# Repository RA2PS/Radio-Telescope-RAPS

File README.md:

# Radio-Telescope-RCA
Radio Telescope System for 1 GHz to 2 GHz Operation

> [!important]
> Make sure to add a KiCad path variable named "RADIO_TELESCOPE_RAPS_PATH"
> for the symbols and footprint to be found on your machine.

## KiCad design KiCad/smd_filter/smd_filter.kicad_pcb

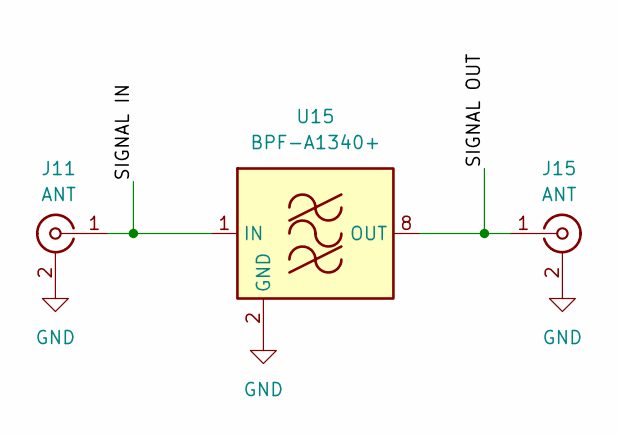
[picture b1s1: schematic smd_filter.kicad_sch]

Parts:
J11, J15: ANT; CONN_142-0711-821_CIN
U15: BPF-A1340+; Mini-Circuits_HQ1157

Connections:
/SMDFilter/GND: J11.2 (Ext), J15.2 (Ext), U15.2 (GND), U15.3 (GND), U15.4 (GND), U15.5 (GND), U15.6 (GND), U15.7 (GND), U15.9 (GND), U15.10 (GND), U15.11 (GND), U15.12 (GND), U15.13 (GND), U15.14 (GND)
/SMDFilter/SIGNAL_IN: J11.1 (In), U15.1 (IN)
/SMDFilter/SIGNAL_OUT: J15.1 (In), U15.8 (OUT)

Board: 2 copper layers, 3 parts (0 on the bottom side), 3 nets, no tracks yet.

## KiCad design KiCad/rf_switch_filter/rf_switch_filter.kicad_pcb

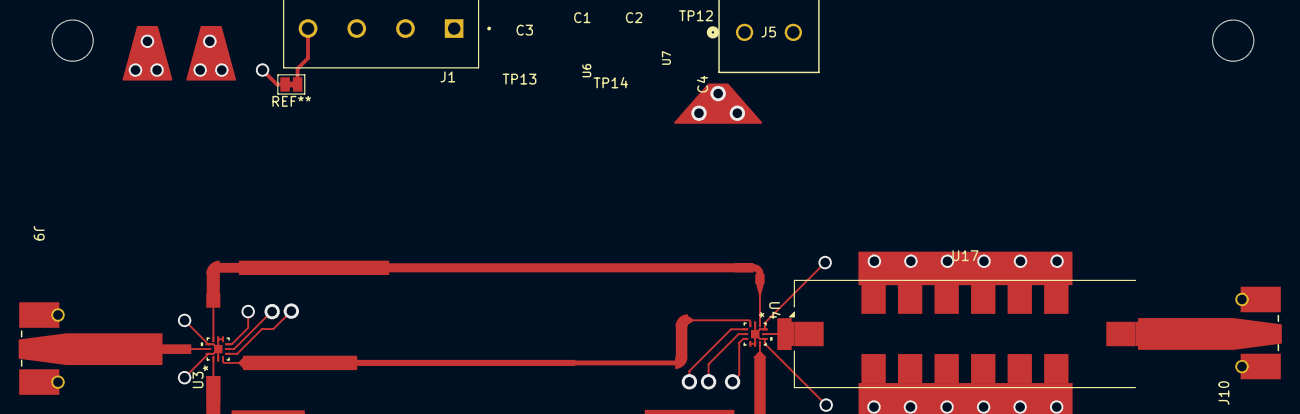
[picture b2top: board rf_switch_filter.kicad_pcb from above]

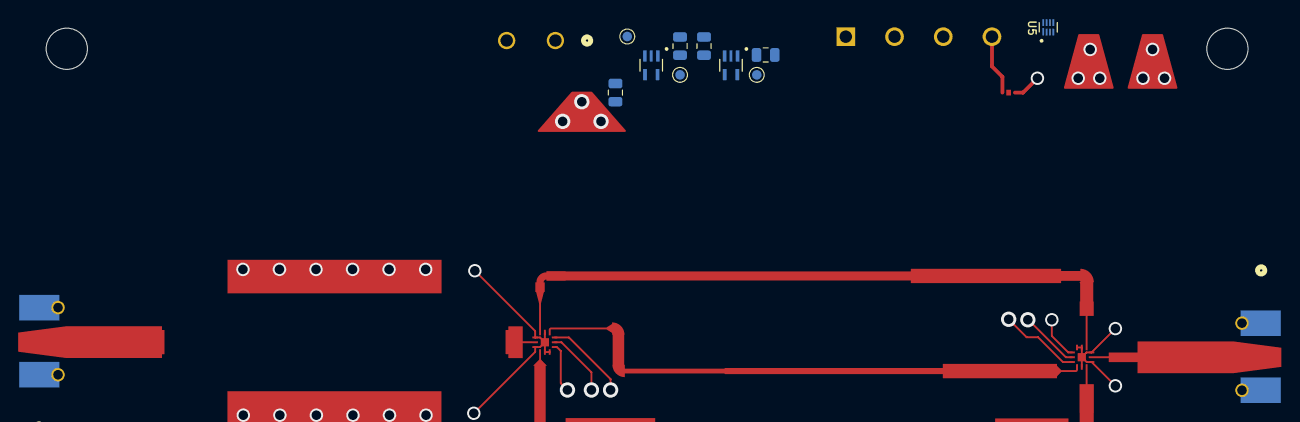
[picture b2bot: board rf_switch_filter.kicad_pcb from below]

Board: 2 copper layers, 17 parts (10 on the bottom side), 15 nets.

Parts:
C1, C2, C3, C4: 1 uF; C_0805_2012Metric
J1: Screw_Terminal_01x04; PHOENIX_1729144
J5: 5V From SDR; CONN_1729128_PXC
J9: ANT; CONN_142-0711-821_CIN
J10: FILTER_OUT; CONN_142-0711-821_CIN
TP12: FCTRL_VIN; TestPoint_Pad_D1.0mm_Edit
TP13: FCTRL_1V8; TestPoint_Pad_D1.0mm_Edit
TP14: FCTRL_3V3; TestPoint_Pad_D1.0mm_Edit
U3, U4: SKY13588-460LF; QFN12_SKY
U5: SN74AVC2T244DQER; SON35P140X100X40-8N
U6: MIC5365-1.8YC5-TR; SOT65P210X110-5N
U7: MIC5365-3.3YC5-TR; SOT65P210X110-5N
U17: BPF-A355; Mini-Circuits_HQ1157

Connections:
/GND: C1.2, C2.2, C3.1, C4.1, J1.1, J5.2, J9.2 (Ext), J10.2 (Ext), U3.2 (GND), U3.7 (GND), U3.8 (GND), U3.10 (GND), U3.12 (GND), U3.13 (EPAD), U4.2 (GND), U4.7 (GND), U4.8 (GND), U4.10 (GND), U4.12 (GND), U4.13 (EPAD), U5.5 (GND), U6.2 (GND), U7.2 (GND), U17.2 (GND), U17.3 (GND), U17.4 (GND), U17.5 (GND), U17.6 (GND), U17.7 (GND), U17.9 (GND), U17.10 (GND), U17.11 (GND), U17.12 (GND), U17.13 (GND), U17.14 (GND)
/RFSwitchFilter/5V: C1.1, C2.1, J5.1, TP12.1, U6.1 (VIN), U6.3 (EN), U7.1 (VIN), U7.3 (EN)
/RFSwitchFilter/+1V8: C3.2, TP13.1, U5.8 (VCCB), U6.5 (VOUT)
/RFSwitchFilter/+3V3: C4.2, TP14.1, U3.6 (VDD), U4.6 (VDD), U7.5 (VOUT)
/RFSwitchFilter/ANT: J9.1 (In), U3.11 (RFC)
/RFSwitchFilter/CNTR_V1: J1.3, U5.2 (A1)
/RFSwitchFilter/CNTR_V2: J1.2, U5.3 (A2)
/RFSwitchFilter/FILTERA_IN: U3.1 (J1), U4.9 (J2)
/RFSwitchFilter/FILTERB_IN: U3.9 (J2), U4.1 (J1)
/RFSwitchFilter/FILTERC_IN: U3.3 (J3), U4.3 (J3)
/RFSwitchFilter/FILTER_OUT: J10.1 (In), U17.8 (OUT)
/RFSwitchFilter/INT_CTRL_V1: U3.4 (V1), U4.5 (V2), U5.7 (B1)
/RFSwitchFilter/INT_CTRL_V2: U3.5 (V2), U4.4 (V1), U5.6 (B2)
/RFSwitchFilter/VDD: J1.4, U5.1 (VCCA), U5.4 (~OE)
unnamed: U4.11 (RFC), U17.1 (IN)

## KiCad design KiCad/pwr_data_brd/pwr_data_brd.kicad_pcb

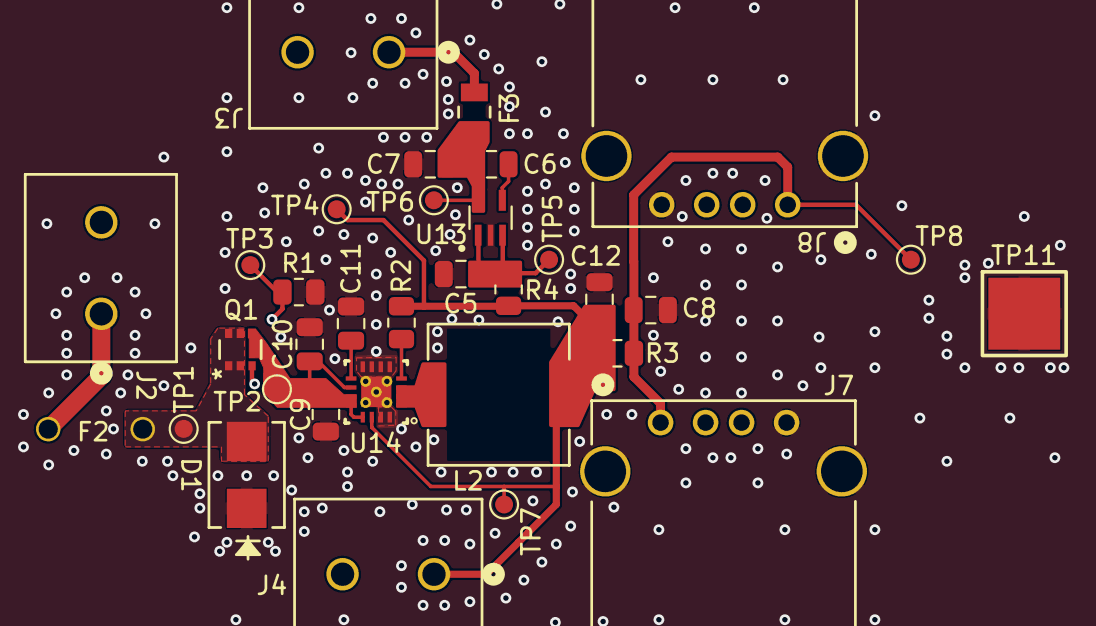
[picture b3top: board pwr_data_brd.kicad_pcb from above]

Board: 2 copper layers, 33 parts (0 on the bottom side), 14 nets.

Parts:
C5, C7: 1 uF; C_0805_2012Metric
C6: 10 nf; C_0805_2012Metric
C8: 10 uF; C_0805_2012Metric
C9: 10uF; C_0805_2012Metric
C10: 0.1uF; C_0805_2012Metric
C11: 3.3nF; C_0805_2012Metric
C12: 22uF; C_0805_2012Metric
D1: SMBJ12A-13-F; SMB_DIO
F2: RGEF300K-2
F3: 0ZCK0020FF2G; 0ZCK_BEL
J2: 9-12V From PoE Splitter; CONN_1729128_PXC
J3: 3V Out For LNA; CONN_1729128_PXC
J4: 5V Out For Filter Board; CONN_1729128_PXC
J7, J8: USB_A; CONN_AU-Y1005-2_ASM
L2: 2.2uH; IND_CB_DRA73
Q1: DMP4047LFDE-7; U-DFN2020-6_DIO
R1, R2: 100k; R_0805_2012Metric
R3, R4: 0; R_0805_2012Metric
TP1: PROCTVIN; TestPoint_Pad_D1.0mm_Edit
TP2: 5VBUCKVIN; TestPoint_Pad_D1.0mm_Edit
TP3: G_PMOS; TestPoint_Pad_D1.0mm_Edit
TP4: 5VBUCKVOUT; TestPoint_Pad_D1.0mm_Edit
TP5: 3VLDOIN; TestPoint_Pad_D1.0mm_Edit
TP6: 3VLDOOUT; TestPoint_Pad_D1.0mm_Edit
TP7: 5VOUT; TestPoint_Pad_D1.0mm_Edit
TP8: 5VUSB; TestPoint_Pad_D1.0mm_Edit
TP11: GNDCLIP; TestPoint_Pad_4.0x4.0mm_Edit
U13: MAX8510EXK30T; SOT65P210X110-5N
U14: TPS62133RGTR; RGT0016C

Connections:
/VOUT_3V: F3.2, J3.1
/VOUT_5V: C12.1, J4.1, L2.2, R2.1, R3.2, R4.2, TP4.1 (1_1), TP7.1 (1_1), U14.14 (VOS)
GND: C5.2, C7.2, C8.2, C9.2, C10.2, C11.1, C12.2, D1.2, J2.2, J3.2, J4.2, J7.4 (GND), J8.4 (GND), R1.2, TP11.1 (1_1), U13.2 (GND), U14.5 (FB), U14.6 (AGND), U14.7 (FSW), U14.8 (DEF), U14.15 (PGND), U14.16 (PGND), U14.17 (EP)
unnamed: C8.1, J7.1 (VBUS), J8.1 (VBUS), R3.1, TP8.1 (1_1)
unnamed: L2.1, U14.1 (SW), U14.2 (SW), U14.3 (SW)
unnamed: D1.1, F2.2, Q1.1 (D), TP1.1 (1_1)
unnamed: Q1.2 (G), R1.1, TP3.1 (1_1)
unnamed: C9.1, C10.1, Q1.3 (S), TP2.1 (1_1), U14.10 (AVIN), U14.11 (PVIN), U14.12 (PVIN), U14.13 (EN)
unnamed: C6.2, U13.4 (BP)
unnamed: C5.1, R4.1, TP5.1 (1_1), U13.1 (IN), U13.3 (~SHDN)
unnamed: C6.1, C7.1, F3.1, TP6.1 (1_1), U13.5 (OUT)
unnamed: R2.2, U14.4 (PG)
unnamed: C11.2, U14.9 (SS_TR)
VDD: F2.1, J2.1

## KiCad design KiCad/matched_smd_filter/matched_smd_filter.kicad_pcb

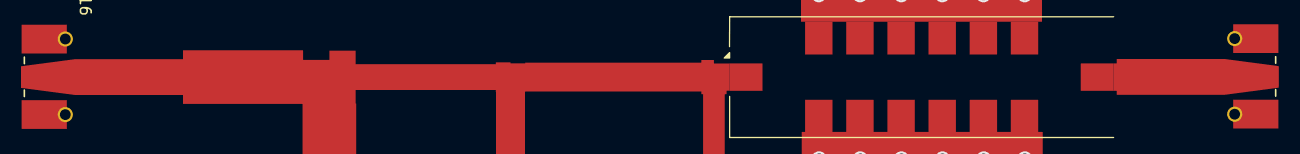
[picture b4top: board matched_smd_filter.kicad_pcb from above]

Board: 2 copper layers, 3 parts (0 on the bottom side), 3 nets, no tracks yet.

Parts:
J16, J17: ANT; CONN_142-0711-821_CIN
U16: BPF-A1340+; Mini-Circuits_HQ1157

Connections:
/Matched SMD Filter/GND: J16.2 (Ext), J17.2 (Ext), U16.2 (GND), U16.3 (GND), U16.4 (GND), U16.5 (GND), U16.6 (GND), U16.7 (GND), U16.9 (GND), U16.10 (GND), U16.11 (GND), U16.12 (GND), U16.13 (GND), U16.14 (GND)
/Matched SMD Filter/SIGNAL_IN: J16.1 (In), U16.1 (IN)
/Matched SMD Filter/SIGNAL_OUT: J17.1 (In), U16.8 (OUT)

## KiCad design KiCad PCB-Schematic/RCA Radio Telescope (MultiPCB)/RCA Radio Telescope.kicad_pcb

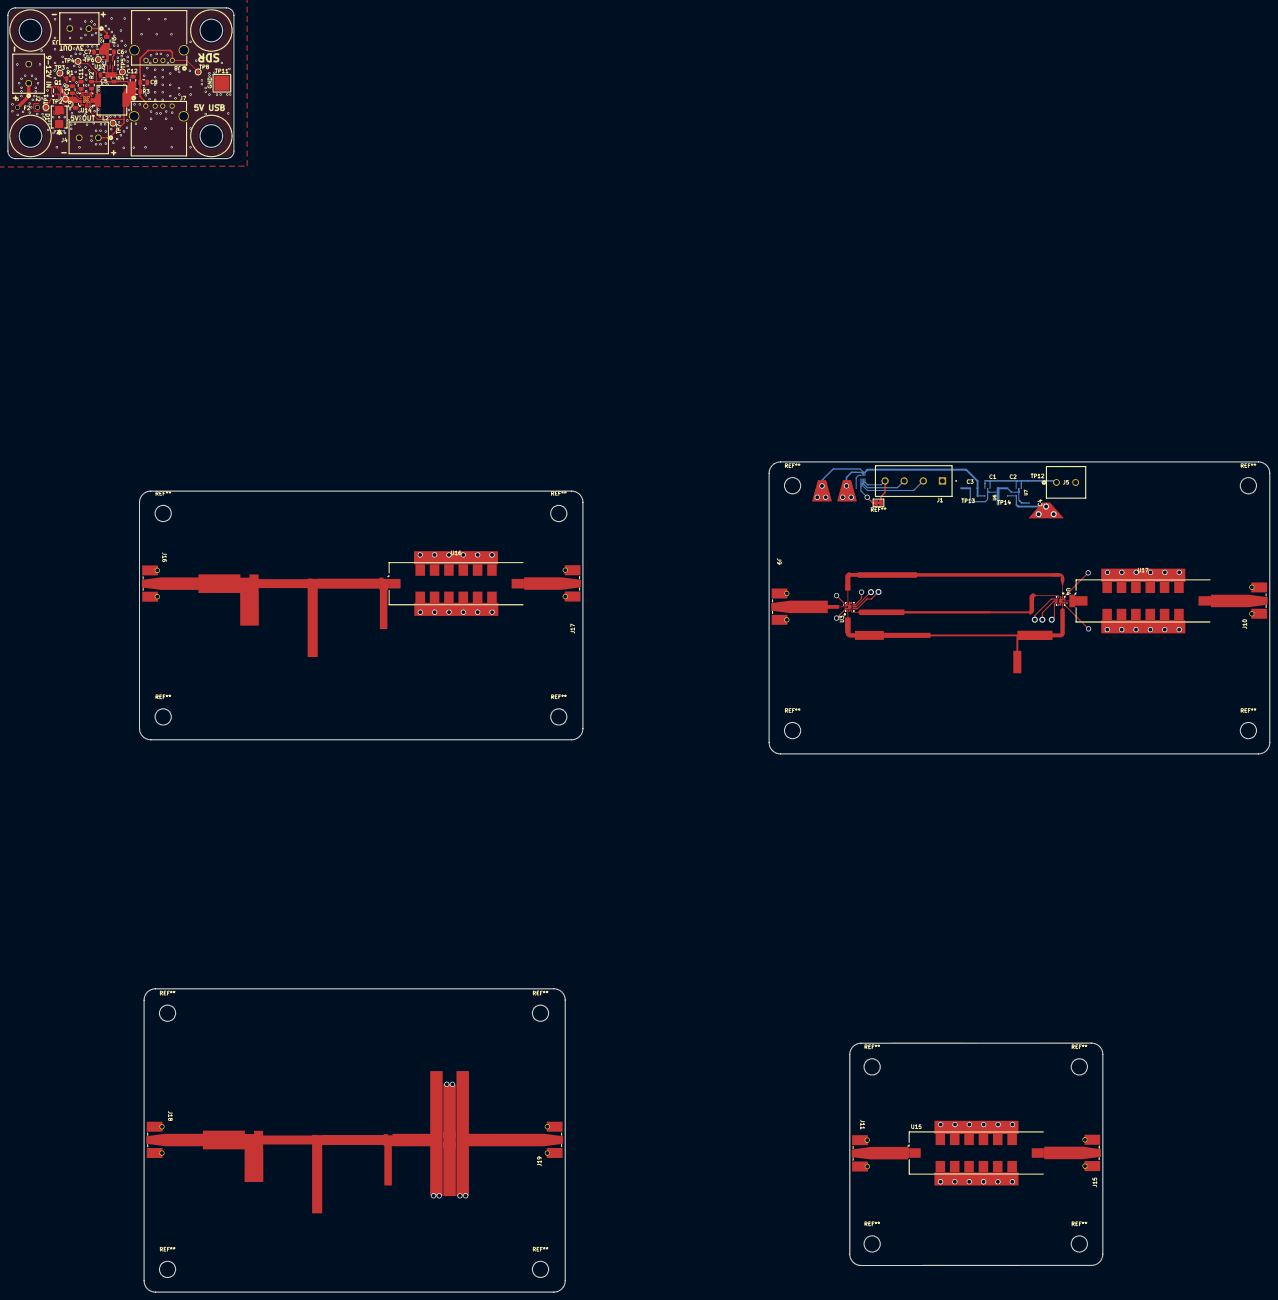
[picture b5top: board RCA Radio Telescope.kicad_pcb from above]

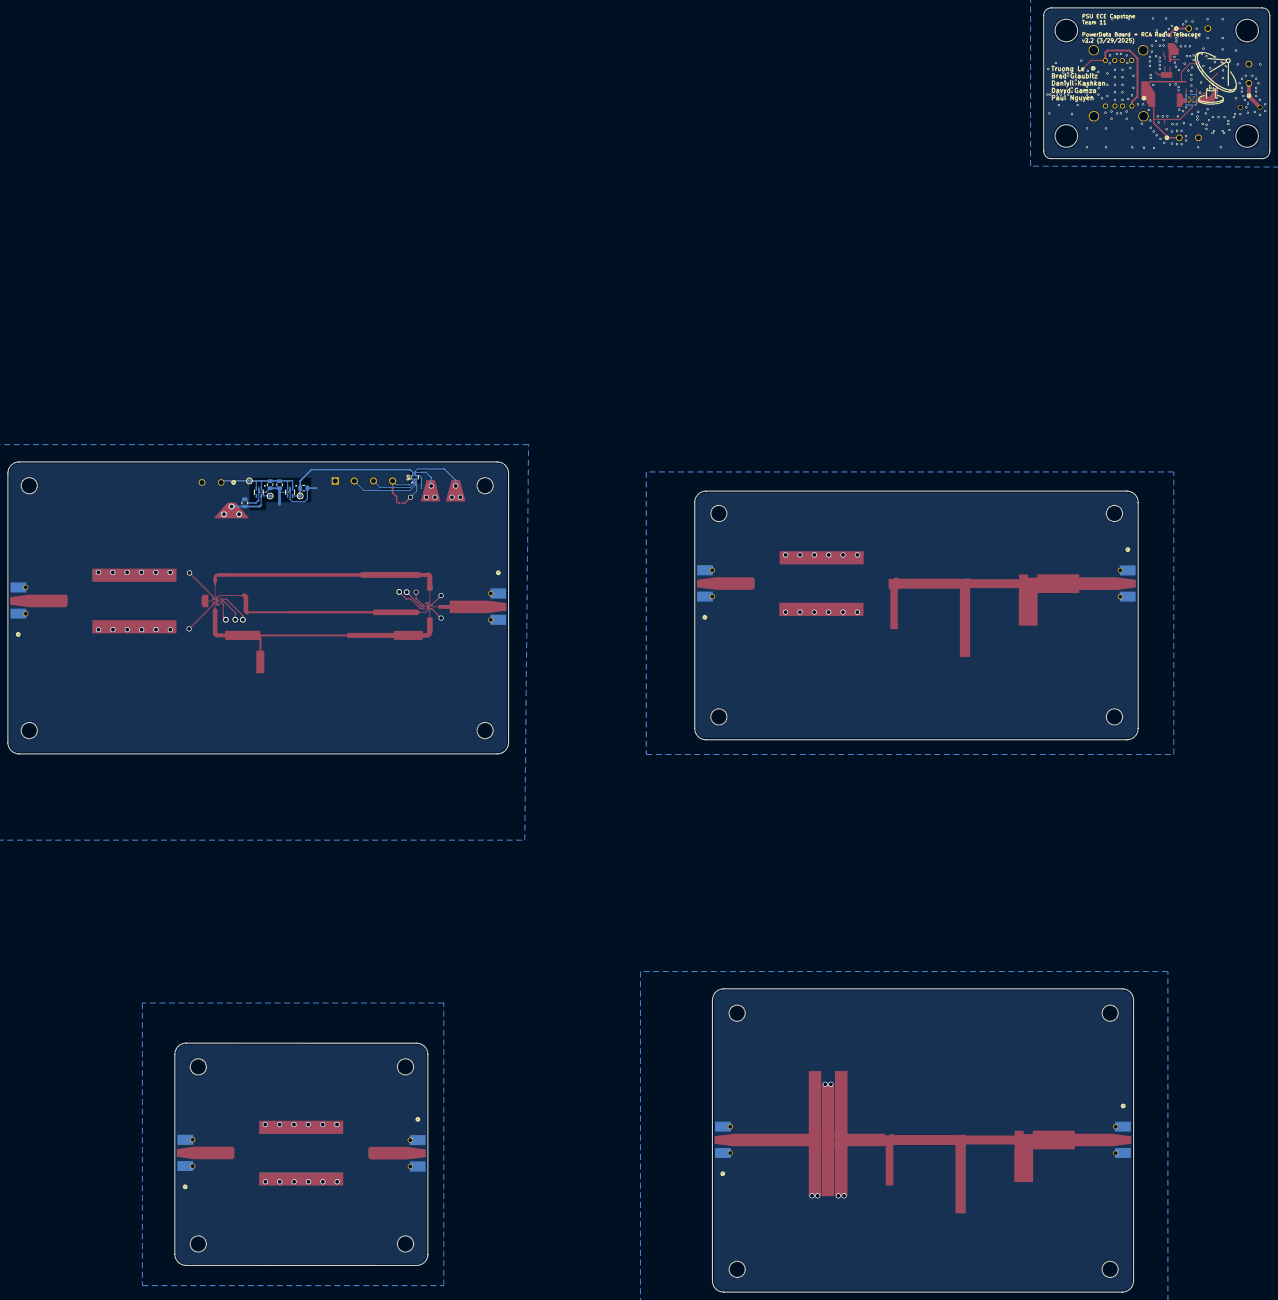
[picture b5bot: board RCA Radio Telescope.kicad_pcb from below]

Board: 2 copper layers, 335.0 x 340.9 mm, 63 parts (10 on the bottom side), 36 nets.

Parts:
C1, C2, C3, C4, C5, C7: 1 uF; C_0805_2012Metric
C6: 10 nf; C_0805_2012Metric
C8: 10 uF; C_0805_2012Metric
C9: 10uF; C_0805_2012Metric
C10: 0.1uF; C_0805_2012Metric
C11: 3.3nF; C_0805_2012Metric
C12: 22uF; C_0805_2012Metric
D1: SMBJ12A-13-F; SMB_DIO
F2: RGEF300K-2
F3: 0ZCK0020FF2G; 0ZCK_BEL
J1: Screw_Terminal_01x04; PHOENIX_1729144
J2: 9-12V From PoE Splitter; CONN_1729128_PXC
J3: 3V Out For LNA; CONN_1729128_PXC
J4: 5V Out For Filter Board; CONN_1729128_PXC
J5: 5V From SDR; CONN_1729128_PXC
J7, J8: USB_A; CONN_AU-Y1005-2_ASM
J9, J11, J15, J16, J17, J18, J19: ANT; CONN_142-0711-821_CIN
J10: FILTER_OUT; CONN_142-0711-821_CIN
L2: 2.2uH; IND_CB_DRA73
MDF: Kikit_Board_Label
MSF: Kikit_Board_Label
PD: Kikit_Board_Label
Q1: DMP4047LFDE-7; U-DFN2020-6_DIO
R1, R2: 100k; R_0805_2012Metric
R3, R4: 0; R_0805_2012Metric
RFS: Kikit_Board_Label
SF: Kikit_Board_Label
TP1: PROCTVIN; TestPoint_Pad_D1.0mm_Edit
TP2: 5VBUCKVIN; TestPoint_Pad_D1.0mm_Edit
TP3: G_PMOS; TestPoint_Pad_D1.0mm_Edit
TP4: 5VBUCKVOUT; TestPoint_Pad_D1.0mm_Edit
TP5: 3VLDOIN; TestPoint_Pad_D1.0mm_Edit
TP6: 3VLDOOUT; TestPoint_Pad_D1.0mm_Edit
TP7: 5VOUT; TestPoint_Pad_D1.0mm_Edit
TP8: 5VUSB; TestPoint_Pad_D1.0mm_Edit
TP11: GNDCLIP; TestPoint_Pad_4.0x4.0mm_Edit
TP12: FCTRL_VIN; TestPoint_Pad_D1.0mm_Edit
TP13: FCTRL_1V8; TestPoint_Pad_D1.0mm_Edit
TP14: FCTRL_3V3; TestPoint_Pad_D1.0mm_Edit
U3, U4: SKY13588-460LF; QFN12_SKY
U5: SN74AVC2T244DQER; SON35P140X100X40-8N
U6: MIC5365-1.8YC5-TR; SOT65P210X110-5N
U7: MIC5365-3.3YC5-TR; SOT65P210X110-5N
U13: MAX8510EXK30T; SOT65P210X110-5N
U14: TPS62133RGTR; RGT0016C
U15, U16: BPF-A1340+; Mini-Circuits_HQ1157
U17: BPF-A355; Mini-Circuits_HQ1157

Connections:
/Matched Distributive Filter/GND: J18.1 (In), J18.2 (Ext), J19.1 (In), J19.2 (Ext)
/Matched SMD Filter/GND: J16.2 (Ext), J17.2 (Ext), U16.2 (GND), U16.3 (GND), U16.4 (GND), U16.5 (GND), U16.6 (GND), U16.7 (GND), U16.9 (GND), U16.10 (GND), U16.11 (GND), U16.12 (GND), U16.13 (GND), U16.14 (GND)
/Matched SMD Filter/SIGNAL_IN: J16.1 (In), U16.1 (IN)
/Matched SMD Filter/SIGNAL_OUT: J17.1 (In), U16.8 (OUT)
/POWERDATA_GND: C5.2, C7.2, C8.2, C9.2, C10.2, C11.1, C12.2, D1.2, J2.2, J3.2, J4.2, J7.4 (GND), J8.4 (GND), R1.2, TP11.1, U13.2 (GND), U14.5 (FB), U14.6 (AGND), U14.7 (FSW), U14.8 (DEF), U14.15 (PGND), U14.16 (PGND), U14.17 (EP)
/PowerDataDistribute/VDD: F2.1, J2.1
/PowerDataDistribute/VOUT_3V: F3.2, J3.1
/PowerDataDistribute/VOUT_5V: C12.1, J4.1, L2.2, R2.1, R3.2, R4.2, TP4.1, TP7.1, U14.14 (VOS)
/RFS_GND: C1.2, C2.2, C3.1, C4.1, J1.1, J5.2, J9.2 (Ext), J10.2 (Ext), U3.2 (GND), U3.7 (GND), U3.8 (GND), U3.10 (GND), U3.12 (GND), U3.13 (EPAD), U4.2 (GND), U4.7 (GND), U4.8 (GND), U4.10 (GND), U4.12 (GND), U4.13 (EPAD), U5.5 (GND), U6.2 (GND), U7.2 (GND), U17.2 (GND), U17.3 (GND), U17.4 (GND), U17.5 (GND), U17.6 (GND), U17.7 (GND), U17.9 (GND), U17.10 (GND), U17.11 (GND), U17.12 (GND), U17.13 (GND), U17.14 (GND)
/RFSwitchFilter/5V_IN: C1.1, C2.1, J5.1, TP12.1, U6.1 (VIN), U6.3 (EN), U7.1 (VIN), U7.3 (EN)
/RFSwitchFilter/+1V8: C3.2, TP13.1, U5.8 (VCCB), U6.5 (VOUT)
/RFSwitchFilter/+3V3: C4.2, TP14.1, U3.6 (VDD), U4.6 (VDD), U7.5 (VOUT)
/RFSwitchFilter/ANT: J9.1 (In), U3.11 (RFC)
/RFSwitchFilter/CNTR_V1: J1.3, U5.2 (A1)
/RFSwitchFilter/CNTR_V2: J1.2, U5.3 (A2)
/RFSwitchFilter/FILTERA_IN: U3.1 (J1), U4.9 (J2)
/RFSwitchFilter/FILTERB_IN: U3.9 (J2), U4.1 (J1)
/RFSwitchFilter/FILTERC_IN: U3.3 (J3), U4.3 (J3)
/RFSwitchFilter/FILTER_OUT: J10.1 (In), U17.8 (OUT)
/RFSwitchFilter/INT_CTRL_V1: U3.4 (V1), U4.5 (V2), U5.7 (B1)
/RFSwitchFilter/INT_CTRL_V2: U3.5 (V2), U4.4 (V1), U5.6 (B2)
/RFSwitchFilter/VDD_REF: J1.4, U5.1 (VCCA), U5.4 (~OE)
/SMDFilter/GND: J11.2 (Ext), J15.2 (Ext), U15.2 (GND), U15.3 (GND), U15.4 (GND), U15.5 (GND), U15.6 (GND), U15.7 (GND), U15.9 (GND), U15.10 (GND), U15.11 (GND), U15.12 (GND), U15.13 (GND), U15.14 (GND)
/SMDFilter/SIGNAL_IN: J11.1 (In), U15.1 (IN)
/SMDFilter/SIGNAL_OUT: J15.1 (In), U15.8 (OUT)
unnamed: C8.1, J7.1 (VBUS), J8.1 (VBUS), R3.1, TP8.1
unnamed: L2.1, U14.1 (SW), U14.2 (SW), U14.3 (SW)
unnamed: D1.1, F2.2, Q1.1 (D), TP1.1
unnamed: Q1.2 (G), R1.1, TP3.1
unnamed: C9.1, C10.1, Q1.3 (S), TP2.1, U14.10 (AVIN), U14.11 (PVIN), U14.12 (PVIN), U14.13 (EN)
unnamed: C6.2, U13.4 (BP)
unnamed: C5.1, R4.1, TP5.1, U13.1 (IN), U13.3 (~SHDN)
unnamed: C6.1, C7.1, F3.1, TP6.1, U13.5 (OUT)
unnamed: R2.2, U14.4 (PG)
unnamed: C11.2, U14.9 (SS_TR)
unnamed: U4.11 (RFC), U17.1 (IN)

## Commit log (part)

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2026-05-28 Move BOM to a subdirectory and delete datasheets
2026-05-28 Copy each board to its own KiCad project
2026-05-28 Move and fix up libraries
2026-05-28 Fix power board symbols and nets, added project specific libs
2026-05-28 Fix filter symbols and labels, added project libraries
2026-05-28 Fix up RF switch project
    Laid out schematic to be more legible, added screw terminals from wiring
    diagram, changed GND symbols, changed labels to be global labels, and
    added project libraries
2026-05-28 Cleanup leftover files and remove recent backup files
2026-05-28 mention path var in README
